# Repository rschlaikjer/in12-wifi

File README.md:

# Wifi-enabled clock with IN-12 nixies

### Nixie clock that synchronizes over Network Time Protocol

Relatively simple Nixie clock, but with an automatic time detection twist.
On boot, and then every hour after, the clock will synchronize with a network
time server to ensure that it is still correct. No need to manually set the
time, no need to worry about RE-setting the time for daylight savings.
The core components are the MCU (ATMEGA328P), WiFi chipset (ATWINC1500)
and boost converter for the nixie tubes (MAX1771).

This project builds on a
[previous clock](https://github.com/rschlaikjer/ntp-nixie)
, which was also NTP-powered but
required a wired internet connection. After the ethernet chipset on that clock
died after a few years continuous service, I resolved to build a second
generation design with two improvements - a seconds place, and wifi enabled to
avoid yet another cable snaking across the desk.

The design is split into three PCBs:
- The control board has three sections - one for the boost logic (12V -> 170V),
  one for the wifi logic (at 3.3V), and one for the MCU itsef at 5V.
- The shift register board, middle, simply converts the serial output from the
  MCU on the control board into a parallel output enabling various sinks on the
  nixie pins through MPSA42 transistors.
- The front PCB simply breaks the nixie pins out into even rows at the edges,
  so that it meshes well with the shift register board. Dealing with routing
  the shift registers, current limiting resistors and transistors all on the
  same board as the nixies was too troublesome compared with simply adding
  another layer.

## BOMs

### Control board

| Part | Value | Device | Package | Description | PROD_ID | VALUE |
| -- | -- | -- | -- | -- | -- | -- |
| C1 | 10uF | CAP0805 | 0805 | Capacitor |  |  |
| C2 | 10uF,25V | CAP_POLPTH2 | CPOL-RADIAL-10UF-25V | Capacitor Polarized |  |  |
| C3 | 10uF/250V | CAP_POLPTH2 | CPOL-RADIAL-10UF-25V | Capacitor Polarized |  |  |
| C4 | 100n | CAPPTH | CAP-PTH-SMALL | Capacitor |  |  |
| C5 | 100n | CAPPTH | CAP-PTH-SMALL | Capacitor |  |  |
| C6 | 100nF | CAP0805 | 0805 | Capacitor |  |  |
| C7 | 10nF | CAP0805 | 0805 | Capacitor |  |  |
| C8 |  | CPOL-USE2,5-6E | E2,5-6E | POLARIZED CAPACITOR, American symbol |  |  |
| C9 |  | CPOL-USE2,5-6E | E2,5-6E | POLARIZED CAPACITOR, American symbol |  |  |
| C10 | 100uF,35V | CAP_POLPTH2 | CPOL-RADIAL-10UF-25V | Capacitor Polarized |  |  |
| C11 | 100nF | CAP0805 | 0805 | Capacitor |  |  |
| C12 | 22pF | CAP0805 | 0805 | Capacitor |  |  |
| C13 | 22pF | CAP0805 | 0805 | Capacitor |  |  |
| C14 | 10uF | CAP0805 | 0805 | Capacitor |  |  |
| C15 |  | CPOL-USE2,5-6E | E2,5-6E | POLARIZED CAPACITOR, American symbol |  |  |
| C16 | 10uF | CAP0805 | 0805 | Capacitor |  |  |
| C17 |  | CPOL-USE2,5-6E | E2,5-6E | POLARIZED CAPACITOR, American symbol |  |  |
| D1 | 1N4007 | 1N4004 | DO41-10 | DIODE |  |  |
| FTDI |  | ARDUINO_SERIAL_PROGRAMPTH | 1X06 | FTDI connector footprints |  |  |
| H1 | STAND-OFF | STAND-OFF | STAND-OFF | #4 Stand Off |  |  |
| H2 | STAND-OFF | STAND-OFF | STAND-OFF | #4 Stand Off |  |  |
| H3 | STAND-OFF | STAND-OFF | STAND-OFF | #4 Stand Off |  |  |
| H4 | STAND-OFF | STAND-OFF | STAND-OFF | #4 Stand Off |  |  |
| IC1 | 7805T | 7805T | TO220H | Positive VOLTAGE REGULATOR |  |  |
| IC3 | ATWINC1500 | ATWINC1500 | ATWINC1500-MR210 | Atmel ATWINC1500-MR210 WiFi/WLAN 802.11 b/g/n |  |  |
| IC4 | LD117AV33 | LD117AV33 | TO220L1 | Low drop fixed and adjustable positive voltage regulators 1 A |  |  |
| ISP1 | AVRISP-6 | AVRISP-6 | AVRISP | AVR ISP HEADER |  |  |
| J1 |  | M04PTH | 1X04 | Header 4 | CONN-09696 |  |
| J2 |  | M02PTH | 1X02 | Standard 2-pin 0.1" header. Use with |  |  |
| J7 |  | M02PTH | 1X02 | Standard 2-pin 0.1" header. Use with |  |  |
| J9 |  | M02PTH | 1X02 | Standard 2-pin 0.1" header. Use with |  |  |
| L1 | 100uH | L-SMT-POWER-B82479 | L-B82479 | SMT power inductors |  |  |
| LED_ACT |  | LED0603 | LED-0603 | LEDs |  |  |
| LED_ERR |  | LED0603 | LED-0603 | LEDs |  |  |
| LED_WIFI |  | LED0603 | LED-0603 | LEDs |  |  |
| Q1 | IRF840 | IRF840 | TO220 | N-Channel Enhancement MOSFET (HEXFET); 500V; 8A; 0,85Ohm |  |  |
| Q2 | MOSFET-NCHANNEL2N7000 | MOSFET-NCHANNEL2N7000 | TO-92 | Common NMOSFET Parts |  |  |
| R1 | 1k | RESISTOR0805-RES | 0805 | Resistor |  |  |
| R2 | 100k | RESISTOR0805-RES | 0805 | Resistor |  |  |
| R3 | 1.5M | RESISTORPTH-1/4W | AXIAL-0.4 | Resistor |  |  |
| R4 | 10k | RESISTORPTH-1/4W | AXIAL-0.4 | Resistor |  |  |
| R5 | 0R050 | RESISTORPTH-1/4W | AXIAL-0.4 | Resistor |  |  |
| R6 | 1lk | RESISTOR0805-RES | 0805 | Resistor |  |  |
| R7 | 1k | RESISTOR0805-RES | 0805 | Resistor |  |  |
| R11 | 100k | RESISTOR0805-RES | 0805 | Resistor |  |  |
| R12 | 100k | RESISTOR0805-RES | 0805 | Resistor |  |  |
| R13 | 100k | RESISTOR0805-RES | 0805 | Resistor |  |  |
| RESET_SW1 | SPST | TACTILE-SWITCH-PTH | TAC-SWITCH-PTH | Tactile Switch 4 Pins, SPST NO |  |  |
| U$3 | MAX1771 | MAX1771 | 8-DIP |  |  |  |
| U$4 | 5k | RTRIM-3362P | RTRIM3362P | BOURNS 3362 - 1/4" Square Trimpot® Trimming Potentiometer |  |  |
| U$19 | PJ-044A | PJ-044A | PJ-044A |  |  |  |
| U1 |  | TXB0104PWRSOIC14 | SO14 | 4-Bit Bi-Directional Level Shifter | IC-11329 |  |
| U2 |  | TXB0104PWRSOIC14 | SO14 | 4-Bit Bi-Directional Level Shifter | IC-11329 |  |
| U3 | ATMEGA328P_TQFP | ATMEGA328P_TQFP | TQFP32-08 |  | IC-09069 | ATMEGA328P_TQFP |
| Y3 | 16MHz | CRYSTALHC49US | HC49US | Various standard crystals. Proven footprints. |  |  |

### Shift register board

| Part | Value | Device | Package | Description | PROD_ID | VALUE |
| -- | -- | -- | -- | -- | -- | -- |
| C1 |  | CAP0805 | 0805 | Capacitor |  |  |
| C2 |  | CAP0805 | 0805 | Capacitor |  |  |
| C3 |  | CAP0805 | 0805 | Capacitor |  |  |
| C4 |  | CAP0805 | 0805 | Capacitor |  |  |
| C5 |  | CAP0805 | 0805 | Capacitor |  |  |
| C6 |  | CAP0805 | 0805 | Capacitor |  |  |
| H1 | STAND-OFF | STAND-OFF | STAND-OFF | #4 Stand Off |  |  |
| H2 | STAND-OFF | STAND-OFF | STAND-OFF | #4 Stand Off |  |  |
| H3 | STAND-OFF | STAND-OFF | STAND-OFF | #4 Stand Off |  |  |
| H4 | STAND-OFF | STAND-OFF | STAND-OFF | #4 Stand Off |  |  |
| IC1 | 74LS595D | 74LS595D | SO16 | 8-bit SHIFT REGISTER, output latch |  |  |
| IC2 | 74LS595D | 74LS595D | SO16 | 8-bit SHIFT REGISTER, output latch |  |  |
| IC3 | 74LS595D | 74LS595D | SO16 | 8-bit SHIFT REGISTER, output latch |  |  |
| IC4 | 74LS595D | 74LS595D | SO16 | 8-bit SHIFT REGISTER, output latch |  |  |
| IC5 | 74LS595D | 74LS595D | SO16 | 8-bit SHIFT REGISTER, output latch |  |  |
| IC9 | 74LS595D | 74LS595D | SO16 | 8-bit SHIFT REGISTER, output latch |  |  |
| J1 |  | M04PTH | 1X04 | Header 4 | CONN-09696 |  |
| J2 |  | M05PTH | 1X05 | Header 5 |  |  |
| J3 |  | M05PTH | 1X05 | Header 5 |  |  |
| J4 |  | M05PTH | 1X05 | Header 5 |  |  |
| J5 |  | M05PTH | 1X05 | Header 5 |  |  |
| J6 |  | M05PTH | 1X05 | Header 5 |  |  |
| J7 |  | M02PTH | 1X02 | Standard 2-pin 0.1" header. Use with |  |  |
| J8 |  | M05PTH | 1X05 | Header 5 |  |  |
| J9 |  | M02PTH | 1X02 | Standard 2-pin 0.1" header. Use with |  |  |
| J10 |  | M05PTH | 1X05 | Header 5 |  |  |
| J11 |  | M05PTH | 1X05 | Header 5 |  |  |
| J12 |  | M05PTH | 1X05 | Header 5 |  |  |
| J13 |  | M05PTH | 1X05 | Header 5 |  |  |
| J14 |  | M05PTH | 1X05 | Header 5 |  |  |
| J15 |  | M05PTH | 1X05 | Header 5 |  |  |
| Q8 | MPSA42 | TRANSISTOR_NPNMPSA42 | SOT23-3 | Generic NPN BJT | TRANS-09116 | MPSA42 |
| Q9 | MPSA42 | TRANSISTOR_NPNMPSA42 | SOT23-3 | Generic NPN BJT | TRANS-09116 | MPSA42 |
| Q10 | MPSA42 | TRANSISTOR_NPNMPSA42 | SOT23-3 | Generic NPN BJT | TRANS-09116 | MPSA42 |
| Q11 | MPSA42 | TRANSISTOR_NPNMPSA42 | SOT23-3 | Generic NPN BJT | TRANS-09116 | MPSA42 |
| Q12 | MPSA42 | TRANSISTOR_NPNMPSA42 | SOT23-3 | Generic NPN BJT | TRANS-09116 | MPSA42 |
| Q13 | MPSA42 | TRANSISTOR_NPNMPSA42 | SOT23-3 | Generic NPN BJT | TRANS-09116 | MPSA42 |
| Q14 | MPSA42 | TRANSISTOR_NPNMPSA42 | SOT23-3 | Generic NPN BJT | TRANS-09116 | MPSA42 |
| Q15 | MPSA42 | TRANSISTOR_NPNMPSA42 | SOT23-3 | Generic NPN BJT | TRANS-09116 | MPSA42 |
| Q16 | MPSA42 | TRANSISTOR_NPNMPSA42 | SOT23-3 | Generic NPN BJT | TRANS-09116 | MPSA42 |
| Q17 | MPSA42 | TRANSISTOR_NPNMPSA42 | SOT23-3 | Generic NPN BJT | TRANS-09116 | MPSA42 |
| Q18 | MPSA42 | TRANSISTOR_NPNMPSA42 | SOT23-3 | Generic NPN BJT | TRANS-09116 | MPSA42 |
| Q19 | MPSA42 | TRANSISTOR_NPNMPSA42 | SOT23-3 | Generic NPN BJT | TRANS-09116 | MPSA42 |
| Q20 | MPSA42 | TRANSISTOR_NPNMPSA42 | SOT23-3 | Generic NPN BJT | TRANS-09116 | MPSA42 |
| Q25 | MPSA42 | TRANSISTOR_NPNMPSA42 | SOT23-3 | Generic NPN BJT | TRANS-09116 | MPSA42 |
| Q26 | MPSA42 | TRANSISTOR_NPNMPSA42 | SOT23-3 | Generic NPN BJT | TRANS-09116 | MPSA42 |
| Q27 | MPSA42 | TRANSISTOR_NPNMPSA42 | SOT23-3 | Generic NPN BJT | TRANS-09116 | MPSA42 |
| Q28 | MPSA42 | TRANSISTOR_NPNMPSA42 | SOT23-3 | Generic NPN BJT | TRANS-09116 | MPSA42 |
| Q29 | MPSA42 | TRANSISTOR_NPNMPSA42 | SOT23-3 | Generic NPN BJT | TRANS-09116 | MPSA42 |
| Q30 | MPSA42 | TRANSISTOR_NPNMPSA42 | SOT23-3 | Generic NPN BJT | TRANS-09116 | MPSA42 |
| Q31 | MPSA42 | TRANSISTOR_NPNMPSA42 | SOT23-3 | Generic NPN BJT | TRANS-09116 | MPSA42 |
| Q32 | MPSA42 | TRANSISTOR_NPNMPSA42 | SOT23-3 | Generic NPN BJT | TRANS-09116 | MPSA42 |
| Q33 | MPSA42 | TRANSISTOR_NPNMPSA42 | SOT23-3 | Generic NPN BJT | TRANS-09116 | MPSA42 |
| Q34 | MPSA42 | TRANSISTOR_NPNMPSA42 | SOT23-3 | Generic NPN BJT | TRANS-09116 | MPSA42 |
| Q35 | MPSA42 | TRANSISTOR_NPNMPSA42 | SOT23-3 | Generic NPN BJT | TRANS-09116 | MPSA42 |
| Q36 | MPSA42 | TRANSISTOR_NPNMPSA42 | SOT23-3 | Generic NPN BJT | TRANS-09116 | MPSA42 |
| Q37 | MPSA42 | TRANSISTOR_NPNMPSA42 | SOT23-3 | Generic NPN BJT | TRANS-09116 | MPSA42 |
| Q38 | MPSA42 | TRANSISTOR_NPNMPSA42 | SOT23-3 | Generic NPN BJT | TRANS-09116 | MPSA42 |
| Q39 | MPSA42 | TRANSISTOR_NPNMPSA42 | SOT23-3 | Generic NPN BJT | TRANS-09116 | MPSA42 |
| Q40 | MPSA42 | TRANSISTOR_NPNMPSA42 | SOT23-3 | Generic NPN BJT | TRANS-09116 | MPSA42 |
| Q45 | MPSA42 | TRANSISTOR_NPNMPSA42 | SOT23-3 | Generic NPN BJT | TRANS-09116 | MPSA42 |
| Q46 | MPSA42 | TRANSISTOR_NPNMPSA42 | SOT23-3 | Generic NPN BJT | TRANS-09116 | MPSA42 |
| Q47 | MPSA42 | TRANSISTOR_NPNMPSA42 | SOT23-3 | Generic NPN BJT | TRANS-09116 | MPSA42 |
| Q48 | MPSA42 | TRANSISTOR_NPNMPSA42 | SOT23-3 | Generic NPN BJT | TRANS-09116 | MPSA42 |
| Q49 | MPSA42 | TRANSISTOR_NPNMPSA42 | SOT23-3 | Generic NPN BJT | TRANS-09116 | MPSA42 |
| Q50 | MPSA42 | TRANSISTOR_NPNMPSA42 | SOT23-3 | Generic NPN BJT | TRANS-09116 | MPSA42 |
| Q51 | MPSA42 | TRANSISTOR_NPNMPSA42 | SOT23-3 | Generic NPN BJT | TRANS-09116 | MPSA42 |
| Q52 | MPSA42 | TRANSISTOR_NPNMPSA42 | SOT23-3 | Generic NPN BJT | TRANS-09116 | MPSA42 |
| Q53 | MPSA42 | TRANSISTOR_NPNMPSA42 | SOT23-3 | Generic NPN BJT | TRANS-09116 | MPSA42 |
| Q54 | MPSA42 | TRANSISTOR_NPNMPSA42 | SOT23-3 | Generic NPN BJT | TRANS-09116 | MPSA42 |
| Q55 | MPSA42 | TRANSISTOR_NPNMPSA42 | SOT23-3 | Generic NPN BJT | TRANS-09116 | MPSA42 |
| Q56 | MPSA42 | TRANSISTOR_NPNMPSA42 | SOT23-3 | Generic NPN BJT | TRANS-09116 | MPSA42 |
| Q57 | MPSA42 | TRANSISTOR_NPNMPSA42 | SOT23-3 | Generic NPN BJT | TRANS-09116 | MPSA42 |
| Q58 | MPSA42 | TRANSISTOR_NPNMPSA42 | SOT23-3 | Generic NPN BJT | TRANS-09116 | MPSA42 |
| Q59 | MPSA42 | TRANSISTOR_NPNMPSA42 | SOT23-3 | Generic NPN BJT | TRANS-09116 | MPSA42 |
| Q60 | MPSA42 | TRANSISTOR_NPNMPSA42 | SOT23-3 | Generic NPN BJT | TRANS-09116 | MPSA42 |
| R3 |  | RESISTOR0805-RES | 0805 | Resistor |  |  |
| R4 |  | RESISTOR0805-RES | 0805 | Resistor |  |  |
| R5 |  | RESISTOR0805-RES | 0805 | Resistor |  |  |
| R6 |  | RESISTOR0805-RES | 0805 | Resistor |  |  |
| R7 |  | RESISTOR0805-RES | 0805 | Resistor |  |  |
| R8 |  | RESISTOR0805-RES | 0805 | Resistor |  |  |
| R9 |  | RESISTOR0805-RES | 0805 | Resistor |  |  |
| R10 |  | RESISTOR0805-RES | 0805 | Resistor |  |  |
| R11 |  | RESISTOR0805-RES | 0805 | Resistor |  |  |
| R12 |  | RESISTOR0805-RES | 0805 | Resistor |  |  |
| U$1 | CTS744 | CTS744 | CT740-746 |  |  |  |
| U$10 | CTS744 | CTS744 | CT740-746 |  |  |  |
| U$11 | CTS744 | CTS744 | CT740-746 |  |  |  |
| U$12 | CTS744 | CTS744 | CT740-746 |  |  |  |
| U$14 | CTS744 | CTS744 | CT740-746 |  |  |  |
| U$15 | CTS744 | CTS744 | CT740-746 |  |  |  |
| U$16 | CTS744 | CTS744 | CT740-746 |  |  |  |
| U$18 | CTS744 | CTS744 | CT740-746 |  |  |  |
| U$19 | CTS744 | CTS744 | CT740-746 |  |  |  |

### Display board

| Part | Value | Device | Package | Description |  |
| -- | -- | -- | -- | -- | -- |
| H1 | STAND-OFF | STAND-OFF | STAND-OFF | #4 Stand Off |  |
| H2 | STAND-OFF | STAND-OFF | STAND-OFF | #4 Stand Off |  |
| H3 | STAND-OFF | STAND-OFF | STAND-OFF | #4 Stand Off |  |
| H4 | STAND-OFF | STAND-OFF | STAND-OFF | #4 Stand Off |  |
| J1 |  | M02PTH | 1X02 | Standard 2-pin 0.1" header. Use with |  |
| J2 |  | M05PTH | 1X05 | Header 5 |  |
| J3 |  | M05PTH | 1X05 | Header 5 |  |
| J4 |  | M05PTH | 1X05 | Header 5 |  |
| J5 |  | M05PTH | 1X05 | Header 5 |  |
| J6 |  | M05PTH | 1X05 | Header 5 |  |
| J7 |  | M05PTH | 1X05 | Header 5 |  |
| J8 |  | M05PTH | 1X05 | Header 5 |  |
| J9 |  | M05PTH | 1X05 | Header 5 |  |
| J10 |  | M05PTH | 1X05 | Header 5 |  |
| J11 |  | M05PTH | 1X05 | Header 5 |  |
| J12 |  | M05PTH | 1X05 | Header 5 |  |
| J13 |  | M05PTH | 1X05 | Header 5 |  |
| N1 | IN-12A | IN-12A | IN-12 | IN-12A: medium numeric topview nixie tube |  |
| N2 | IN-12A | IN-12A | IN-12 | IN-12A: medium numeric topview nixie tube |  |
| N3 | IN-12A | IN-12A | IN-12 | IN-12A: medium numeric topview nixie tube |  |
| N4 | IN-12A | IN-12A | IN-12 | IN-12A: medium numeric topview nixie tube |  |
| N5 | IN-12A | IN-12A | IN-12 | IN-12A: medium numeric topview nixie tube |  |
| N6 | IN-12A | IN-12A | IN-12 | IN-12A: medium numeric topview nixie tube |  |
| R1 |  | RESISTOR0805-RES | 0805 | Resistor |  |
| R2 |  | RESISTOR0805-RES | 0805 | Resistor |  |
| R3 |  | RESISTOR0805-RES | 0805 | Resistor |  |
| R4 |  | RESISTOR0805-RES | 0805 | Resistor |  |
| R5 |  | RESISTOR0805-RES | 0805 | Resistor |  |
| R6 |  | RESISTOR0805-RES | 0805 | Resistor |  |

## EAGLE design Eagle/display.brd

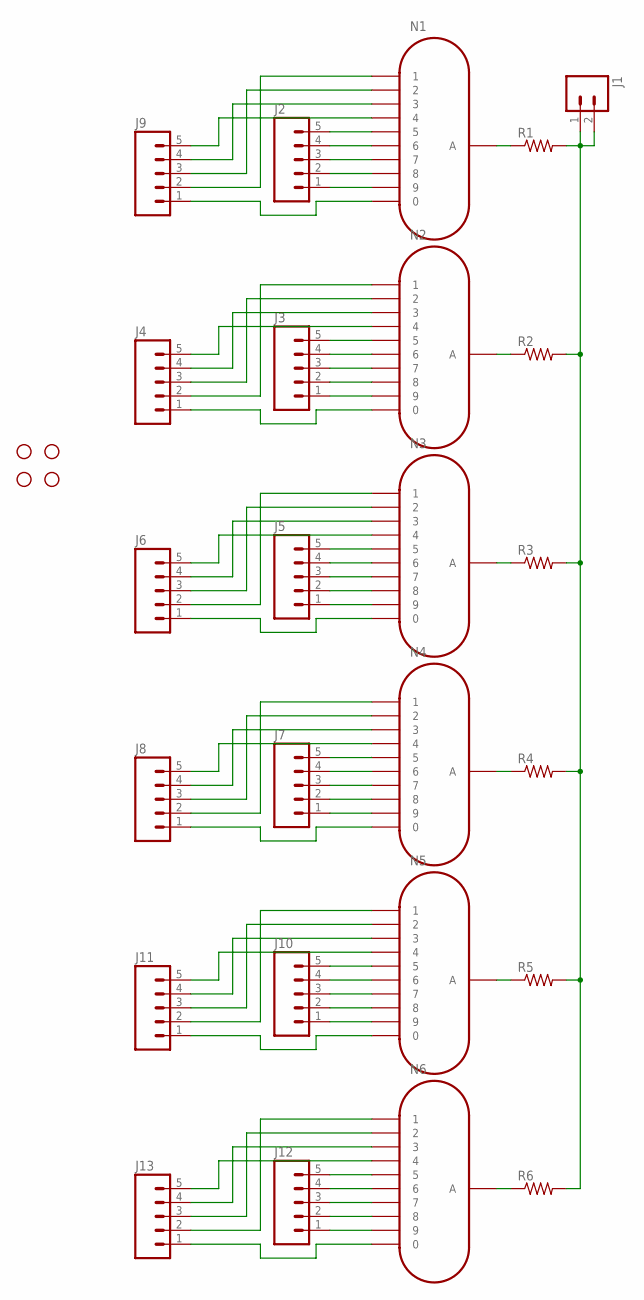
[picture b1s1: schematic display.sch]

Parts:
H1, H2, H3, H4: STAND-OFF
J1: M02PTH; 1X02
J2, J3, J4, J5, J6, J7, J8, J9, J10, J11, J12, J13: M05PTH; 1X05
N1, N2, N3, N4, N5, N6: IN-12A; IN-12
R1, R2, R3, R4, R5, R6: RESISTOR0805-RES; 0805

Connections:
unnamed: J4.1, N2.0
unnamed: J3.1, N2.9
unnamed: J3.2, N2.8
unnamed: J3.3, N2.7
unnamed: J3.4, N2.6
unnamed: J4.3, N2.2
unnamed: J4.4, N2.3
unnamed: J4.5, N2.4
unnamed: J3.5, N2.5
unnamed: J4.2, N2.1
unnamed: J2.1, N1.9
unnamed: J2.2, N1.8
unnamed: J2.3, N1.7
unnamed: J2.4, N1.6
unnamed: J2.5, N1.5
unnamed: J9.2, N1.1
unnamed: J9.3, N1.2
unnamed: J9.4, N1.3
unnamed: J9.5, N1.4
unnamed: J9.1, N1.0
unnamed: J6.1, N3.0
unnamed: J5.1, N3.9
unnamed: J5.2, N3.8
unnamed: J5.3, N3.7
unnamed: J5.4, N3.6
unnamed: J5.5, N3.5
unnamed: J6.2, N3.1
unnamed: J6.3, N3.2
unnamed: J6.4, N3.3
unnamed: J6.5, N3.4
unnamed: J8.1, N4.0
unnamed: J7.1, N4.9
unnamed: J7.2, N4.8
unnamed: J7.3, N4.7
unnamed: J7.4, N4.6
unnamed: J7.5, N4.5
unnamed: J8.2, N4.1
unnamed: J8.3, N4.2
unnamed: J8.4, N4.3
unnamed: J8.5, N4.4
unnamed: J11.1, N5.0
unnamed: J10.1, N5.9
unnamed: J10.2, N5.8
unnamed: J10.3, N5.7
unnamed: J10.4, N5.6
unnamed: J10.5, N5.5
unnamed: J11.2, N5.1
unnamed: J11.3, N5.2
unnamed: J11.4, N5.3
unnamed: J11.5, N5.4
unnamed: J13.1, N6.0
unnamed: J12.1, N6.9
unnamed: J12.2, N6.8
unnamed: J12.3, N6.7
unnamed: J12.4, N6.6
unnamed: J12.5, N6.5
unnamed: J13.2, N6.1
unnamed: J13.3, N6.2
unnamed: J13.4, N6.3
unnamed: J13.5, N6.4
unnamed: N1.A, R1.1
unnamed: N2.A, R2.1
unnamed: N3.A, R3.1
unnamed: N4.A, R4.1
unnamed: N5.A, R5.1
unnamed: N6.A, R6.1
unnamed: J1.1, J1.2, R1.2, R2.2, R3.2, R4.2, R5.2, R6.2

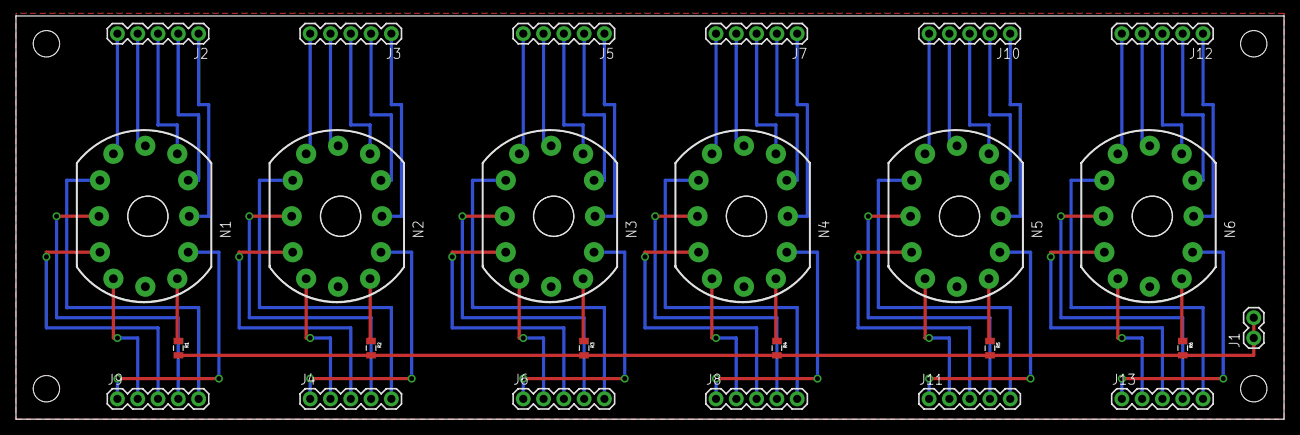
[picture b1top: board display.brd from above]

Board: 2 copper layers, 158.7 x 50.5 mm, 29 parts (0 on the bottom side), 67 nets.

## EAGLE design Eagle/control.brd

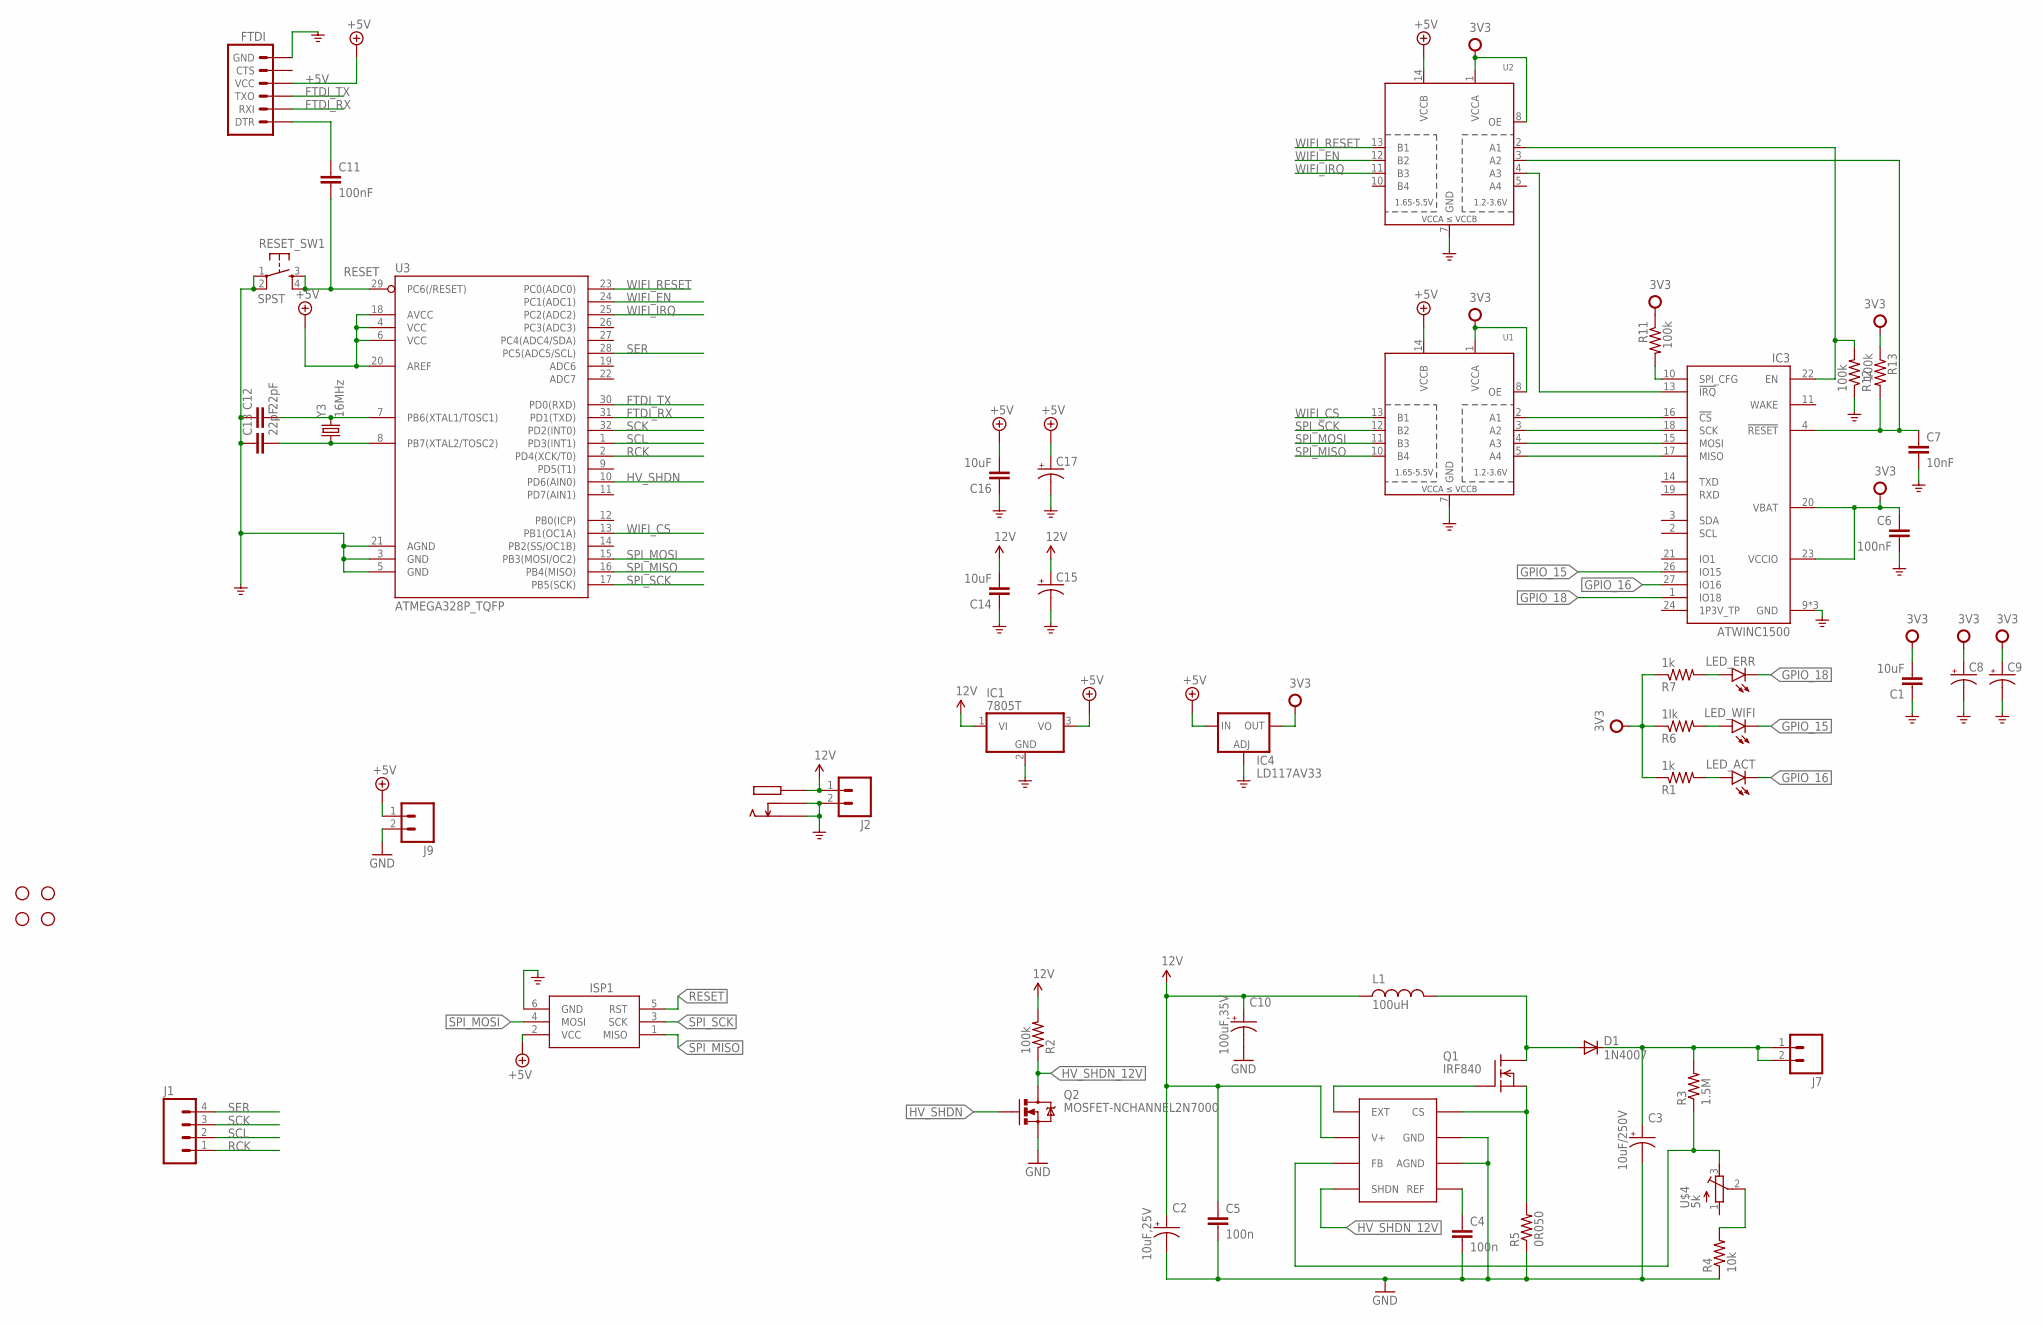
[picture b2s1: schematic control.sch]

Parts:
C1, C14, C16: 10uF; 0805
C2: 10uF,25V; CPOL-RADIAL-10UF-25V
C3: 10uF/250V; CPOL-RADIAL-10UF-25V
C4, C5: 100n; CAP-PTH-SMALL
C6, C11: 100nF; 0805
C7: 10nF; 0805
C8, C9, C15, C17: CPOL-USE2,5-6E; E2,5-6E
C10: 100uF,35V; CPOL-RADIAL-10UF-25V
C12, C13: 22pF; 0805
D1: 1N4007; DO41-10
FTDI: ARDUINO_SERIAL_PROGRAMPTH; 1X06
H1, H2, H3, H4: STAND-OFF
IC1: 7805T; TO220H
IC3: ATWINC1500; ATWINC1500-MR210
IC4: LD117AV33; TO220L1
ISP1: AVRISP-6; AVRISP
J1: M04PTH; 1X04
J2, J7, J9: M02PTH; 1X02
L1: 100uH; L-B82479
LED_ACT: LED0603; LED-0603
LED_ERR: LED0603; LED-0603
LED_WIFI: LED0603; LED-0603
Q1: IRF840; TO220
Q2: MOSFET-NCHANNEL2N7000; TO-92
R1, R7: 1k; 0805
R2, R11, R12, R13: 100k; 0805
R3: 1.5M; AXIAL-0.4
R4: 10k; AXIAL-0.4
R5: 0R050; AXIAL-0.4
R6: 1lk; 0805
RESET_SW1: SPST; TAC-SWITCH-PTH
U1, U2: TXB0104PWRSOIC14; SO14
U3: ATMEGA328P_TQFP; TQFP32-08
U$3: MAX1771; 8-DIP
U$4: 5k; RTRIM3362P
U$19: PJ-044A
Y3: 16MHz; HC49US

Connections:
12V: C2.1 (+), C5.1, C10.1 (+), C14.2, C15.+, IC1.1 (VI), J2.1, L1.P$1 (1), R2.2, U$3.V+, U$19.1, U$19.P1 (1)
+3V3: C1.2, C6.1, C8.+, C9.+, IC3.20 (VBAT), IC3.23 (VCCIO), IC4.2 (OUT), R1.1, R6.1, R7.1, R11.1, R13.1, U1.1 (VCCA), U1.8 (OE), U2.1 (VCCA), U2.8 (OE)
+5V: C16.2, C17.+, FTDI.4 (VCC), IC1.3 (VO), IC4.3 (IN), ISP1.2 (VCC), J9.1, U1.14 (VCCB), U2.14 (VCCB), U3.4 (VCC), U3.6 (VCC), U3.18 (AVCC), U3.20 (AREF)
EXT1: Q1.1 (G), U$3.EXT
FTDI_RX: FTDI.2 (RXI), U3.31 (PD1(TXD))
FTDI_TX: FTDI.3 (TXO), U3.30 (PD0(RXD))
GND: C1.1, C2.2 (-), C3.2 (-), C4.2, C5.2, C6.2, C7.2, C8.-, C9.-, C10.2 (-), C12.1, C13.1, C14.1, C15.-, C16.1, C17.-, FTDI.6 (GND), IC1.2 (GND), IC3.9 (GND), IC3.12 (GND), IC3.28 (GND), IC4.1 (ADJ), ISP1.6 (GND), J2.2, J9.2, Q2.1 (S), R4.P$1 (1), R5.P$1 (1), R12.1, RESET_SW1.1, RESET_SW1.2, U1.7 (GND), U2.7 (GND), U3.3 (GND), U3.5 (GND), U3.21 (AGND), U$3.AGND, U$3.GND, U$19.2, U$19.3, U$19.P2 (2), U$19.P3 (3)
GPIO_15: IC3.26 (IO15), LED_WIFI.C
GPIO_16: IC3.27 (IO16), LED_ACT.C
GPIO_18: IC3.1 (IO18), LED_ERR.C
HV_GEIGER: C3.1 (+), D1.C, J7.1, J7.2, R3.P$2 (2)
HV_SHDN: Q2.2 (G), U3.10 (PD6(AIN0))
HV_SHDN_12V: Q2.3 (D), R2.1, U$3.SHDN
unnamed: R3.P$1 (1), U$3.FB, U$4.3
unnamed: D1.A, L1.P$2 (2), Q1.2 (D)
unnamed: Q1.3 (S), R5.P$2 (2), U$3.CS
unnamed: C4.1, U$3.REF
unnamed: R4.P$2 (2), U$4.2
unnamed: LED_ACT.A, R1.2
unnamed: IC3.10 (SPI_CFG), R11.2
unnamed: LED_WIFI.A, R6.2
unnamed: LED_ERR.A, R7.2
unnamed: IC3.16 (!CS), U1.2 (A1)
unnamed: IC3.18 (SCK), U1.3 (A2)
unnamed: IC3.15 (MOSI), U1.4 (A3)
unnamed: IC3.17 (MISO), U1.5 (A4)
unnamed: IC3.13 (!IRQ), U2.4 (A3)
unnamed: IC3.22 (EN), R12.2, U2.2 (A1)
unnamed: C12.2, U3.7 (PB6(XTAL1/TOSC1)), Y3.2
unnamed: C13.2, U3.8 (PB7(XTAL2/TOSC2)), Y3.1
unnamed: C7.1, IC3.4 (!RESET), R13.2, U2.3 (A2)
unnamed: C11.1, FTDI.1 (DTR)
RCK: J1.1, U3.2 (PD4(XCK/T0))
RESET: C11.2, ISP1.5 (RST), RESET_SW1.3, RESET_SW1.4, U3.29 (PC6(/RESET))
SCK: J1.3, U3.32 (PD2(INT0))
SCL: J1.2, U3.1 (PD3(INT1))
SER: J1.4, U3.28 (PC5(ADC5/SCL))
SPI_MISO: ISP1.1 (MISO), U1.10 (B4), U3.16 (PB4(MISO))
SPI_MOSI: ISP1.4 (MOSI), U1.11 (B3), U3.15 (PB3(MOSI/OC2))
SPI_SCK: ISP1.3 (SCK), U1.12 (B2), U3.17 (PB5(SCK))
WIFI_CS: U1.13 (B1), U3.13 (PB1(OC1A))
WIFI_EN: U2.12 (B2), U3.24 (PC1(ADC1))
WIFI_IRQ: U2.11 (B3), U3.25 (PC2(ADC2))
WIFI_RESET: U2.13 (B1), U3.23 (PC0(ADC0))

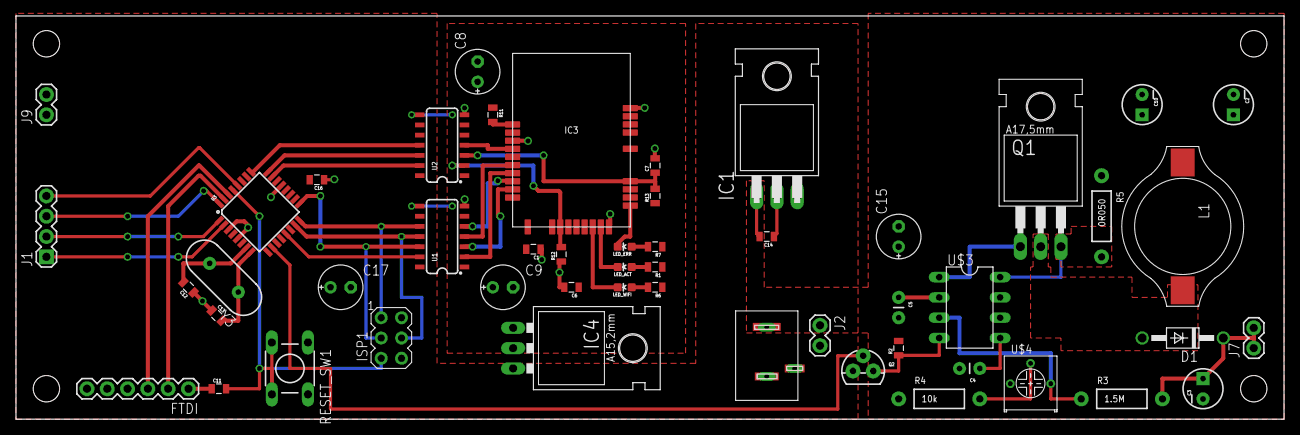
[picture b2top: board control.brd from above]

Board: 2 copper layers, 158.6 x 50.3 mm, 55 parts (0 on the bottom side), 44 nets.

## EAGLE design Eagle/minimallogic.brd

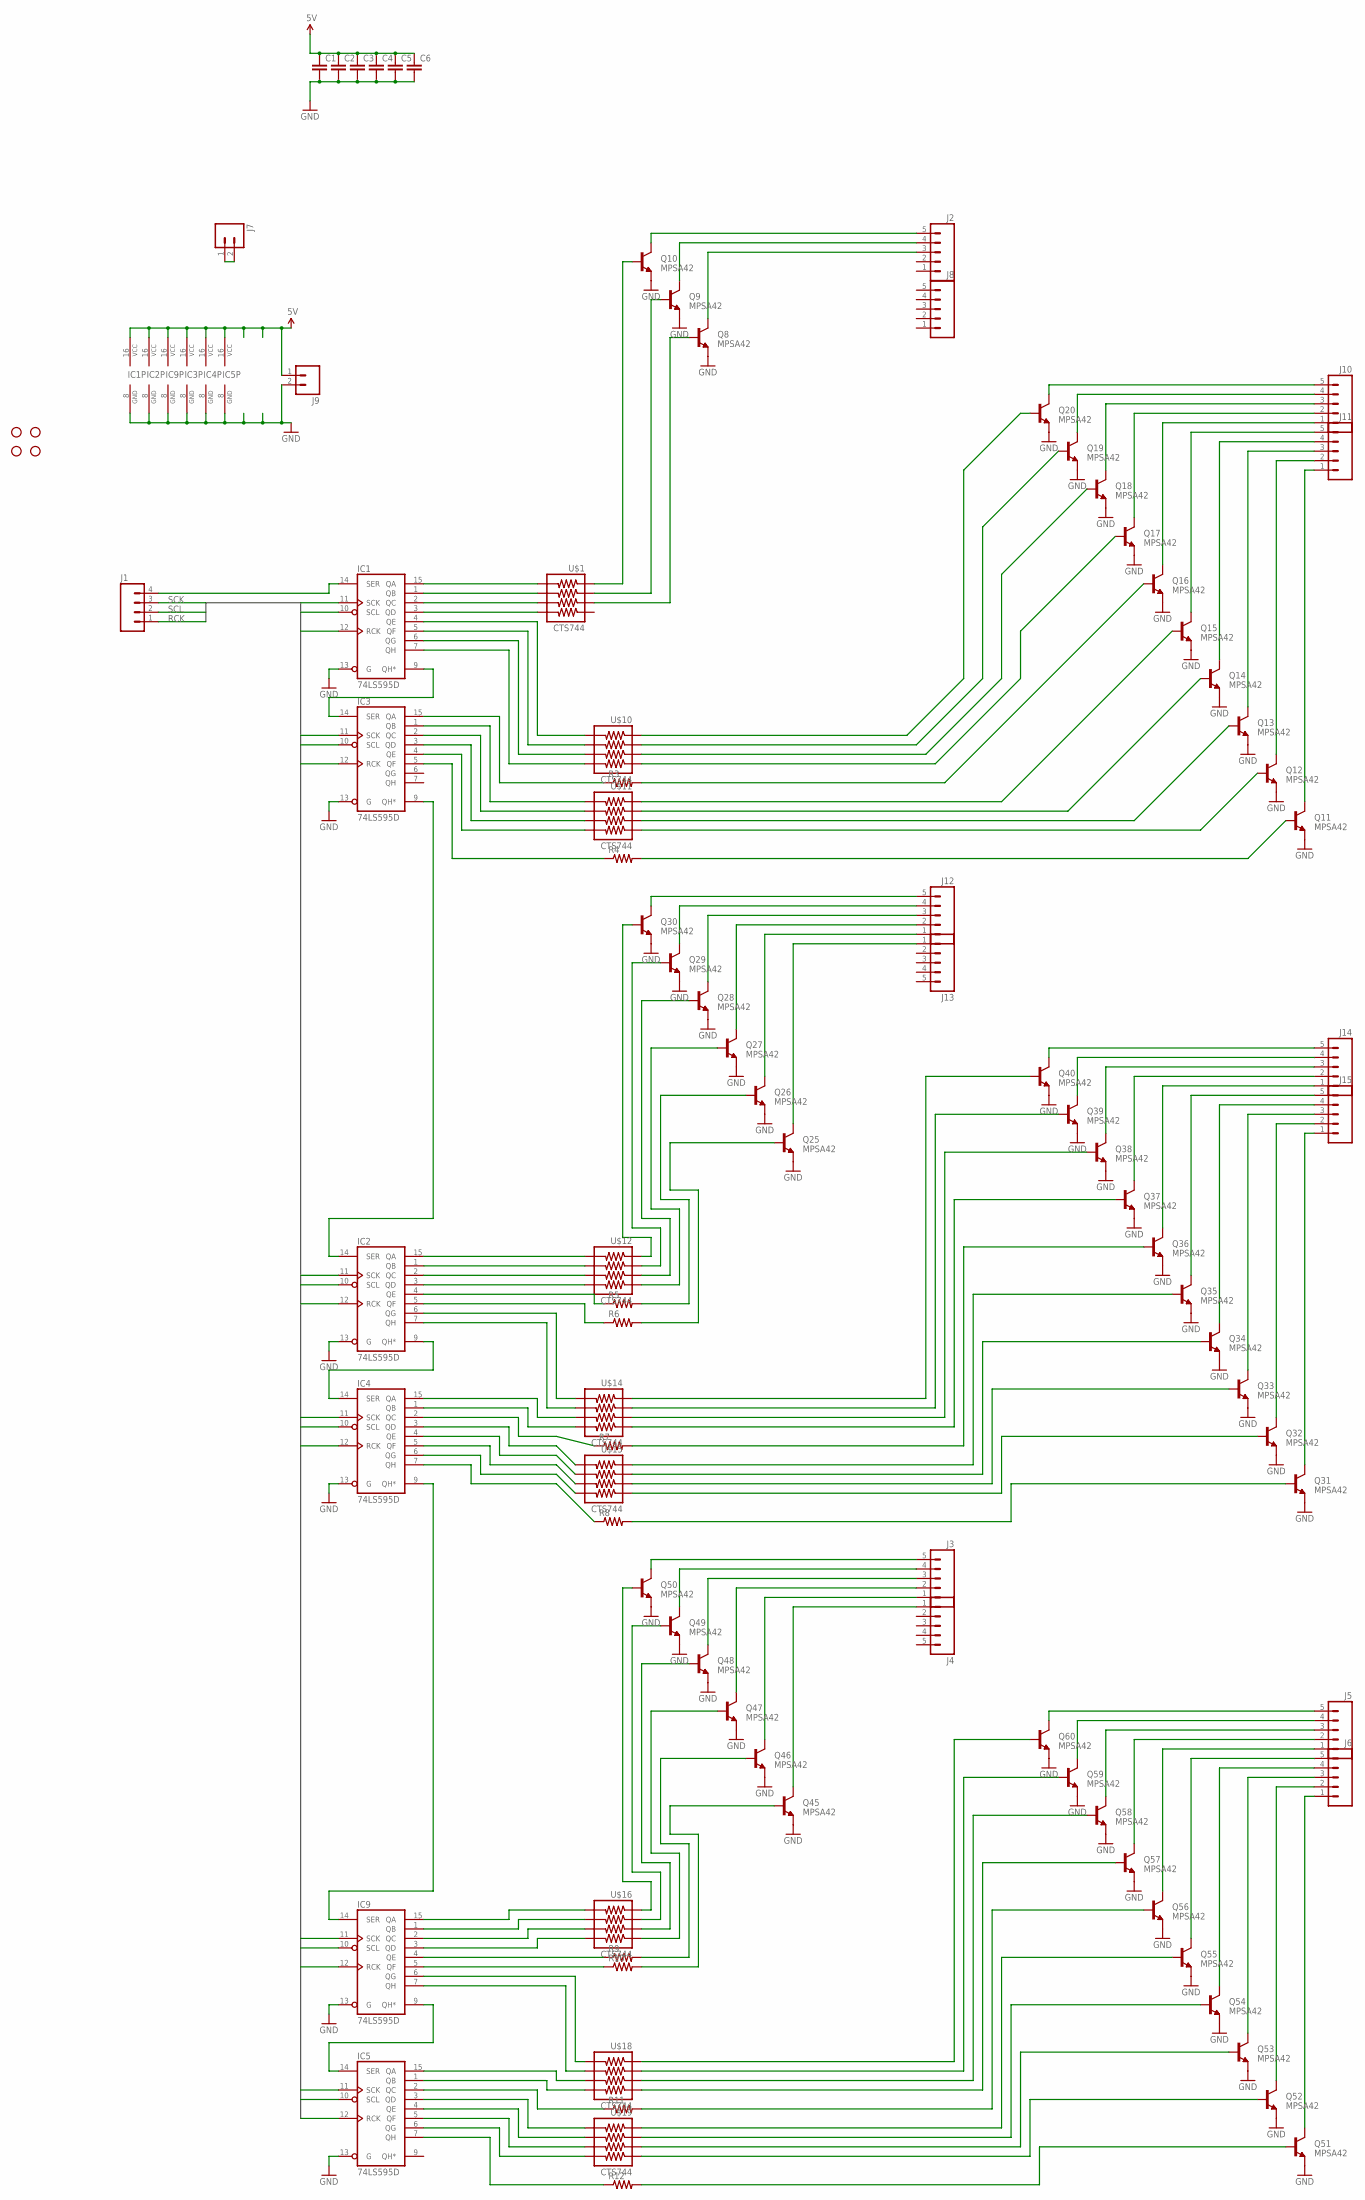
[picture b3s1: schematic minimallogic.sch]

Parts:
C1, C2, C3, C4, C5, C6: CAP0805; 0805
H1, H2, H3, H4: STAND-OFF
IC1, IC2, IC3, IC4, IC5, IC9: 74LS595D; SO16
J1: M04PTH; 1X04
J2, J3, J4, J5, J6, J8, J10, J11, J12, J13, J14, J15: M05PTH; 1X05
J7, J9: M02PTH; 1X02
Q8, Q9, Q10, Q11, Q12, Q13, Q14, Q15, Q16, Q17, Q18, Q19, Q20, Q25, Q26, Q27, Q28, Q29, Q30, Q31, Q32, Q33, Q34, Q35, Q36, Q37, Q38, Q39, Q40, Q45, Q46, Q47, Q48, Q49, Q50, Q51, Q52, Q53, Q54, Q55, Q56, Q57, Q58, Q59, Q60: MPSA42; SOT23-3
R3, R4, R5, R6, R7, R8, R9, R10, R11, R12: RESISTOR0805-RES; 0805
U$1, U$10, U$11, U$12, U$14, U$15, U$16, U$18, U$19: CTS744; CT740-746

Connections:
5V: C1.1, C2.1, C3.1, C4.1, C5.1, C6.1, IC1.16 (VCC), IC2.16 (VCC), IC3.16 (VCC), IC4.16 (VCC), IC5.16 (VCC), IC9.16 (VCC), J9.1
GND: C1.2, C2.2, C3.2, C4.2, C5.2, C6.2, IC1.8 (GND), IC1.13 (G), IC2.8 (GND), IC2.13 (G), IC3.8 (GND), IC3.13 (G), IC4.8 (GND), IC4.13 (G), IC5.8 (GND), IC5.13 (G), IC9.8 (GND), IC9.13 (G), J9.2, Q8.2 (E), Q9.2 (E), Q10.2 (E), Q11.2 (E), Q12.2 (E), Q13.2 (E), Q14.2 (E), Q15.2 (E), Q16.2 (E), Q17.2 (E), Q18.2 (E), Q19.2 (E), Q20.2 (E), Q25.2 (E), Q26.2 (E), Q27.2 (E), Q28.2 (E), Q29.2 (E), Q30.2 (E), Q31.2 (E), Q32.2 (E), Q33.2 (E), Q34.2 (E), Q35.2 (E), Q36.2 (E), Q37.2 (E), Q38.2 (E), Q39.2 (E), Q40.2 (E), Q45.2 (E), Q46.2 (E), Q47.2 (E), Q48.2 (E), Q49.2 (E), Q50.2 (E), Q51.2 (E), Q52.2 (E), Q53.2 (E), Q54.2 (E), Q55.2 (E), Q56.2 (E), Q57.2 (E), Q58.2 (E), Q59.2 (E), Q60.2 (E)
unnamed: IC1.4 (QE), U$10.P8 (OUT1)
unnamed: IC1.5 (QF), U$10.P7 (OUT2)
unnamed: IC1.6 (QG), U$10.P6 (OUT3)
unnamed: IC1.7 (QH), U$10.P5 (OUT4)
unnamed: IC2.5 (QF), R6.1
unnamed: IC2.4 (QE), R5.1
unnamed: IC2.9 (QH*), IC4.14 (SER)
unnamed: IC9.15 (QA), U$16.P8 (OUT1)
unnamed: J13.1, Q25.3 (C)
unnamed: J12.1, Q26.3 (C)
unnamed: J11.1, Q11.3 (C)
unnamed: J11.2, Q12.3 (C)
unnamed: J11.3, Q13.3 (C)
unnamed: J11.4, Q14.3 (C)
unnamed: J11.5, Q15.3 (C)
unnamed: J10.1, Q16.3 (C)
unnamed: J10.2, Q17.3 (C)
unnamed: J10.3, Q18.3 (C)
unnamed: J10.4, Q19.3 (C)
unnamed: J10.5, Q20.3 (C)
unnamed: IC1.9 (QH*), IC3.14 (SER)
unnamed: IC1.15 (QA), U$1.P8 (OUT1)
unnamed: IC1.1 (QB), U$1.P7 (OUT2)
unnamed: IC1.2 (QC), U$1.P6 (OUT3)
unnamed: IC1.3 (QD), U$1.P5 (OUT4)
unnamed: IC3.15 (QA), R3.1
unnamed: IC3.1 (QB), U$11.P8 (OUT1)
unnamed: IC3.2 (QC), U$11.P7 (OUT2)
unnamed: IC3.3 (QD), U$11.P6 (OUT3)
unnamed: IC3.4 (QE), U$11.P5 (OUT4)
unnamed: IC3.5 (QF), R4.1
unnamed: IC9.1 (QB), U$16.P7 (OUT2)
unnamed: IC9.2 (QC), U$16.P6 (OUT3)
unnamed: IC9.3 (QD), U$16.P5 (OUT4)
unnamed: IC9.4 (QE), R9.1
unnamed: IC9.5 (QF), R10.1
unnamed: IC2.15 (QA), U$12.P8 (OUT1)
unnamed: IC2.1 (QB), U$12.P7 (OUT2)
unnamed: IC2.2 (QC), U$12.P6 (OUT3)
unnamed: IC2.3 (QD), U$12.P5 (OUT4)
unnamed: IC5.14 (SER), IC9.9 (QH*)
unnamed: J12.2, Q27.3 (C)
unnamed: IC4.9 (QH*), IC9.14 (SER)
unnamed: IC9.6 (QG), U$18.P8 (OUT1)
unnamed: IC9.7 (QH), U$18.P7 (OUT2)
unnamed: IC5.15 (QA), U$18.P6 (OUT3)
unnamed: IC2.6 (QG), U$14.P8 (OUT1)
unnamed: IC2.7 (QH), U$14.P7 (OUT2)
unnamed: IC4.15 (QA), U$14.P6 (OUT3)
unnamed: IC4.1 (QB), U$14.P5 (OUT4)
unnamed: IC4.2 (QC), R7.1
unnamed: IC4.3 (QD), U$15.P8 (OUT1)
unnamed: IC4.4 (QE), U$15.P7 (OUT2)
unnamed: IC4.5 (QF), U$15.P6 (OUT3)
unnamed: IC4.6 (QG), U$15.P5 (OUT4)
unnamed: IC4.7 (QH), R8.1
unnamed: IC5.1 (QB), U$18.P5 (OUT4)
unnamed: IC5.2 (QC), R11.1
unnamed: IC5.3 (QD), U$19.P8 (OUT1)
unnamed: IC5.4 (QE), U$19.P7 (OUT2)
unnamed: Q20.1 (B), U$10.P1 (IN1)
unnamed: IC5.5 (QF), U$19.P6 (OUT3)
unnamed: IC5.6 (QG), U$19.P5 (OUT4)
unnamed: IC5.7 (QH), R12.1
unnamed: J4.1, Q45.3 (C)
unnamed: J3.1, Q46.3 (C)
unnamed: J3.2, Q47.3 (C)
unnamed: J7.1, J7.2
unnamed: Q11.1 (B), R4.2
unnamed: J12.3, Q28.3 (C)
unnamed: J12.4, Q29.3 (C)
unnamed: Q12.1 (B), U$11.P4 (IN4)
unnamed: J12.5, Q30.3 (C)
unnamed: Q13.1 (B), U$11.P3 (IN3)
unnamed: Q14.1 (B), U$11.P2 (IN2)
unnamed: Q15.1 (B), U$11.P1 (IN1)
unnamed: Q16.1 (B), R3.2
unnamed: Q19.1 (B), U$10.P2 (IN2)
unnamed: Q18.1 (B), U$10.P3 (IN3)
unnamed: Q17.1 (B), U$10.P4 (IN4)
unnamed: Q10.1 (B), U$1.P1 (IN1)
unnamed: Q9.1 (B), U$1.P2 (IN2)
unnamed: Q8.1 (B), U$1.P3 (IN3)
unnamed: J15.1, Q31.3 (C)
unnamed: J15.2, Q32.3 (C)
unnamed: J15.3, Q33.3 (C)
unnamed: J15.4, Q34.3 (C)
unnamed: J15.5, Q35.3 (C)
unnamed: J14.1, Q36.3 (C)
unnamed: J14.2, Q37.3 (C)
unnamed: J14.3, Q38.3 (C)
unnamed: J14.4, Q39.3 (C)
unnamed: J14.5, Q40.3 (C)
unnamed: Q30.1 (B), U$12.P1 (IN1)
unnamed: Q29.1 (B), U$12.P2 (IN2)
unnamed: Q28.1 (B), U$12.P3 (IN3)
unnamed: Q27.1 (B), U$12.P4 (IN4)
unnamed: Q26.1 (B), R5.2
unnamed: Q25.1 (B), R6.2
unnamed: IC2.14 (SER), IC3.9 (QH*)
unnamed: J2.3, Q8.3 (C)
unnamed: J2.4, Q9.3 (C)
unnamed: J2.5, Q10.3 (C)
unnamed: Q40.1 (B), U$14.P1 (IN1)
unnamed: Q39.1 (B), U$14.P2 (IN2)
unnamed: Q38.1 (B), U$14.P3 (IN3)
unnamed: Q37.1 (B), U$14.P4 (IN4)
unnamed: Q36.1 (B), R7.2
unnamed: Q35.1 (B), U$15.P1 (IN1)
unnamed: Q34.1 (B), U$15.P2 (IN2)
unnamed: Q33.1 (B), U$15.P3 (IN3)
unnamed: Q32.1 (B), U$15.P4 (IN4)
unnamed: Q31.1 (B), R8.2
unnamed: Q50.1 (B), U$16.P1 (IN1)
unnamed: Q49.1 (B), U$16.P2 (IN2)
unnamed: Q48.1 (B), U$16.P3 (IN3)
unnamed: Q47.1 (B), U$16.P4 (IN4)
unnamed: Q46.1 (B), R9.2
unnamed: Q45.1 (B), R10.2
unnamed: Q60.1 (B), U$18.P1 (IN1)
unnamed: Q59.1 (B), U$18.P2 (IN2)
unnamed: Q58.1 (B), U$18.P3 (IN3)
unnamed: Q57.1 (B), U$18.P4 (IN4)
unnamed: Q56.1 (B), R11.2
unnamed: Q55.1 (B), U$19.P1 (IN1)
unnamed: Q54.1 (B), U$19.P2 (IN2)
unnamed: Q53.1 (B), U$19.P3 (IN3)
unnamed: Q52.1 (B), U$19.P4 (IN4)
unnamed: Q51.1 (B), R12.2
unnamed: IC1.14 (SER), J1.4
unnamed: J3.3, Q48.3 (C)
unnamed: J3.4, Q49.3 (C)
unnamed: J3.5, Q50.3 (C)
unnamed: J6.1, Q51.3 (C)
unnamed: J6.2, Q52.3 (C)
unnamed: J6.3, Q53.3 (C)
unnamed: J6.4, Q54.3 (C)
unnamed: J6.5, Q55.3 (C)
unnamed: J5.1, Q56.3 (C)
unnamed: J5.2, Q57.3 (C)
unnamed: J5.3, Q58.3 (C)
unnamed: J5.4, Q59.3 (C)
unnamed: J5.5, Q60.3 (C)
RCK: IC1.12 (RCK), IC2.12 (RCK), IC3.12 (RCK), IC4.12 (RCK), IC5.12 (RCK), IC9.12 (RCK), J1.1
SCK: IC1.11 (SCK), IC2.11 (SCK), IC3.11 (SCK), IC4.11 (SCK), IC5.11 (SCK), IC9.11 (SCK), J1.3
SCL: IC1.10 (SCL), IC2.10 (SCL), IC3.10 (SCL), IC4.10 (SCL), IC5.10 (SCL), IC9.10 (SCL), J1.2

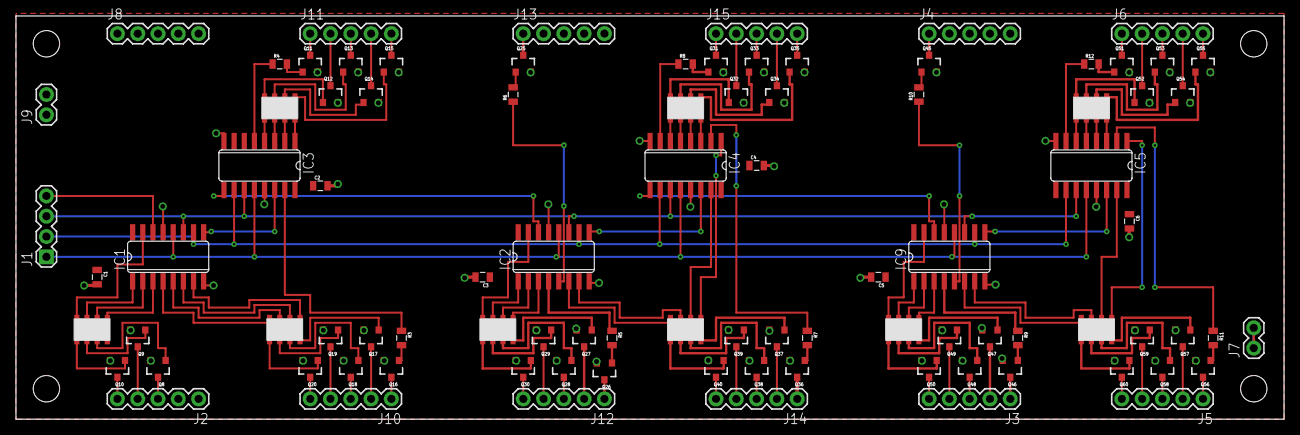
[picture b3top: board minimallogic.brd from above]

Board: 2 copper layers, 158.7 x 50.5 mm, 95 parts (0 on the bottom side), 148 nets.

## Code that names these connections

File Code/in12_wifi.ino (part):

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
// Wifi control
#define WIFI_SS 9
#define WIFI_IRQ 16
#define WIFI_RESET 15
#define WIFI_EN 14

// Shift register control
#define N_SER 19
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
    // Wifi
    pinMode(WIFI_SS, OUTPUT);
    pinMode(WIFI_IRQ, OUTPUT);
    pinMode(WIFI_RESET, OUTPUT);
    pinMode(WIFI_EN, OUTPUT);

    // Shift register
    pinMode(N_SER, OUTPUT);
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    //// Start wifi
    digitalWrite(WIFI_EN, HIGH);
    delay(250);
    WiFi.setPins(WIFI_SS, WIFI_IRQ, WIFI_RESET, -1);

    // Turn on display
    write595Time(0, 0, 0);
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
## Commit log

2017-06-29 Import arduino sketch
2017-06-29 Add the EAGLE files
2017-06-29 Add some media
2017-06-29 Add a README
2017-06-29 Center smaller image
2017-09-10 Copy over some firmware updates

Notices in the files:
parts and their libraries:
SparkFun-Connectors: Licensing: Creative Commons ShareAlike 4.0 International - https://creativecommons.org/licenses/by-sa/4.0
